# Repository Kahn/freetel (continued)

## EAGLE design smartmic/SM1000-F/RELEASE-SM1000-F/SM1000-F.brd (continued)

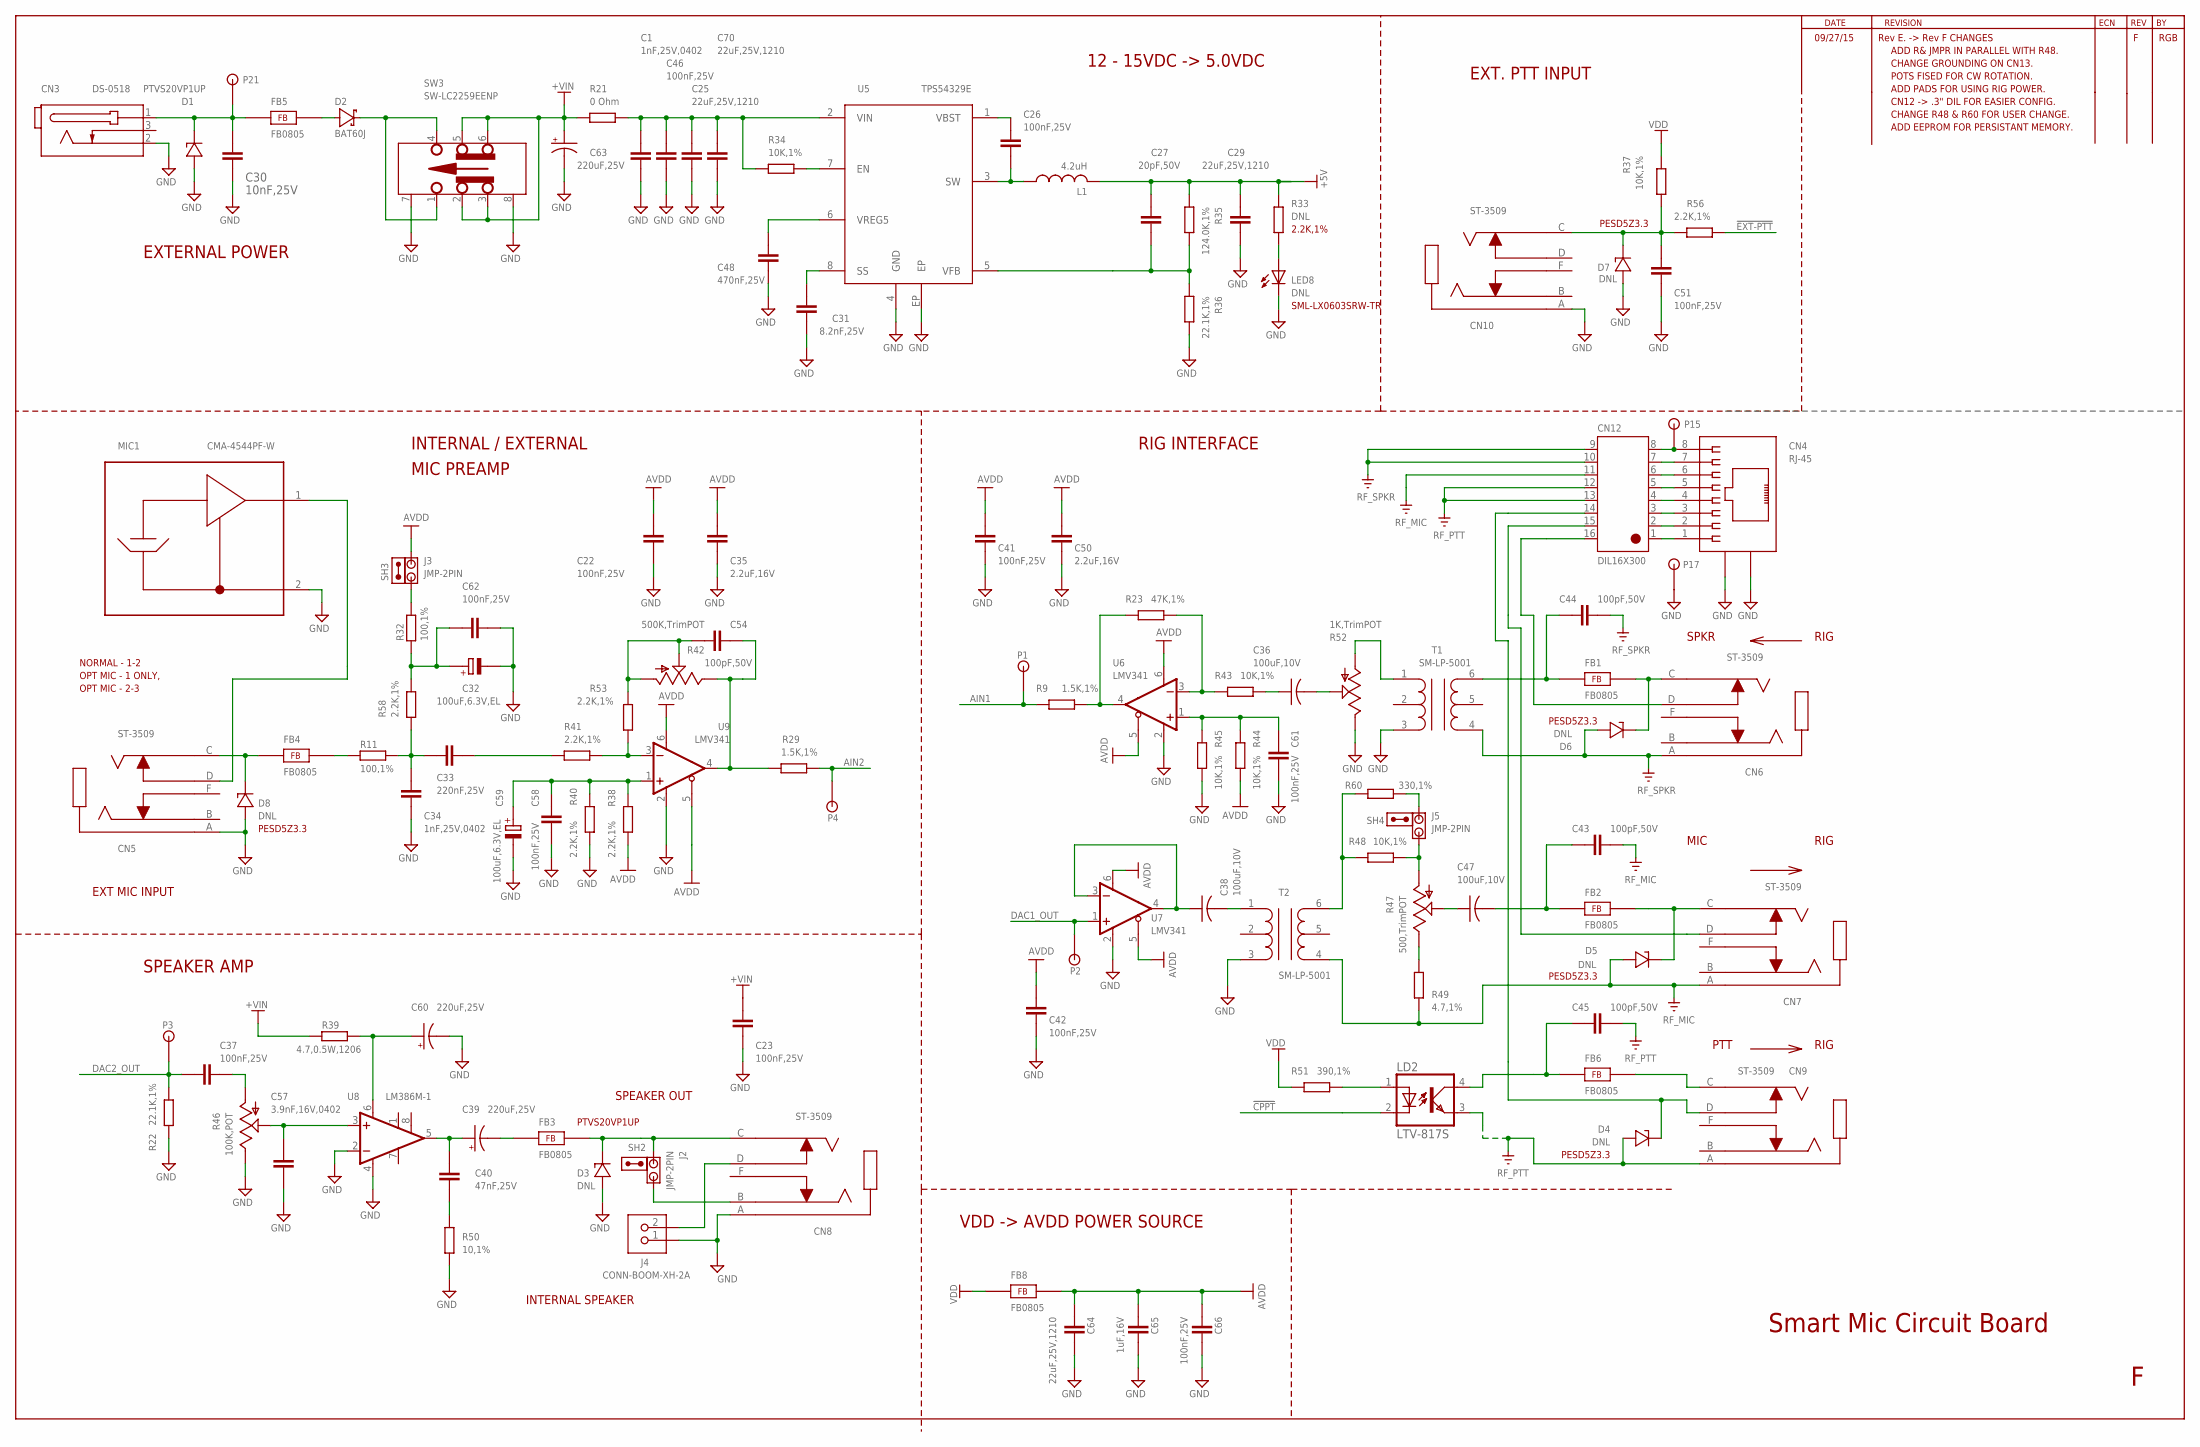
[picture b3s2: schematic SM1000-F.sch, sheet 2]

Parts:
C1, C34: 1nF,25V,0402; CAPC1005X60N
C22, C23, C26, C37, C41, C42, C46, C51, C58, C61, C62, C66: 100nF,25V; CAPC1005X60N
C25, C29, C64, C70: 22uF,25V,1210; CAPC3225X168N
C27: 20pF,50V; CAPC1005X60N
C30: 10nF,25V; CAPC1005X60N
C31: 8.2nF,25V; CAPC1608X92N
C32, C59: 100uF,6.3V,EL; NICHICON-WX-6.3
C33: 220nF,25V; CAPC1005X60N
C35, C50: 2.2uF,16V; CAPC1608X92N
C36, C38, C47: 100uF,10V; C1210
C39, C60, C63: 220uF,25V; CAP-CHEMI-HA0
C40: 47nF,25V; CAPC1005X60N
C43, C44, C45, C54: 100pF,50V; CAPC1005X60N
C48: 470nF,25V; CAPC1608X92N
C57: 3.9nF,16V,0402; CAPC1005X60N
C65: 1uF,16V; CAPC1608X92N
CN3: DS-0518
CN4: RJ-45; CONN-RJ45-MOLEX-44144-003
CN5, CN6, CN7, CN8, CN9, CN10: ST-3509
CN12: DIL16X300
D1: PTVS20VP1UP; SOD128
D2: BAT60J; SOD323R_INFINEON
D3: DNL; SOD128
D4, D5, D6, D7, D8: DNL; SOD523
FB1, FB2, FB3, FB4, FB5, FB6, FB8: FB0805; FE0805
J2, J3, J5: JMP-2PIN; JMPR-2PIN
J4: CONN-BOOM-XH-2A
L1: 4.2uH; SRR5028
LD2: LTV-817S
LED8: DNL; SML-LX0603SRW
MIC1: CMA-4544PF-W
P1, P2, P3, P4, P15, P17, P21: TPAD50
R9, R29: 1.5K,1%; RESC1005X40AN
R11, R32: 100,1%; RESC1608X55N
R21: 0 Ohm; RESC1608X55N
R22: 22.1K,1%; RESC1608X55N
R23: 47K,1%; RESC1005X40AN
R33: DNL; RESC1005X40AN
R34, R37, R43, R44, R45: 10K,1%; RESC1005X40AN
R35: 124.0K,1%; RESC1005X40AN
R36: 22.1K,1%; RESC1005X40AN
R38, R40, R41, R53, R56, R58: 2.2K,1%; RESC1005X40AN
R39: 4.7,0.5W,1206; RESC3115X70N
R42: 500K,TrimPOT; POT3361
R46: 100K,POT; POT-3310C
R47: 500,TrimPOT; POT3361
R48: 10K,1%; RESC3115X70N
R49: 4.7,1%; RESC1005X40AN
R50: 10,1%; RESC1608X55N
R51: 390,1%; RESC1005X40AN
R52: 1K,TrimPOT; POT3361
R60: 330,1%; RESC3115X70N
SH2, SH3, SH4: SHUNT,0.1IN; NOPACKAGE
SW3: SW-LC2259EENP; SW-LC2259
T1, T2: SM-LP-5001
U5: TPS54329E; PSO-DDA
U6, U7, U9: LMV341; SOT23-6
U8: LM386M-1; SO08

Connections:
!CPPT!: LD2.2 (C); also elsewhere on the board
!EXT-PTT!: R56.2; also elsewhere on the board
+5V: C27.1, C29.1, L1.2, R33.1, R35.1; also elsewhere on the board
+VIN: C23.1, C63.1, R21.1, R39.1, SW3.2, SW3.3, SW3.5, SW3.6; also elsewhere on the board
AIN1: P1.1, R9.1; also elsewhere on the board
AIN2: P4.1, R29.1; also elsewhere on the board
APTT: CN9.D, CN12.14, D4.C
AVDD: C22.1, C35.1, C41.1, C42.1, C50.1, C64.1, C65.1, C66.1, FB8.2, J3.2, R38.2, R44.2, U6.5 (!SHDN!), U6.6 (V+), U7.5 (!SHDN!), U7.6 (V+), U9.5 (!SHDN!), U9.6 (V+)
DAC1_OUT: P2.1, U7.1 (+IN); also elsewhere on the board
DAC2_OUT: C37.1, P3.1, R22.1; also elsewhere on the board
GND: C1.1, C22.2, C23.2, C25.2, C29.2, C30.2, C31.2, C32.2 (-), C34.2, C35.2, C41.2, C42.2, C46.2, C48.2, C50.2, C51.2, C57.2, C58.1, C59.2 (-), C60.2, C61.2, C62.2, C63.2, C64.2, C65.2, C66.2, C70.2, CN3.2, CN4.9, CN4.10, CN5.A, CN8.A, CN10.A, D1.A, D3.A, D7.A, D8.A, J4.1, LED8.C, MIC1.2, P17.1, R22.2, R36.2, R40.2, R45.2, R46.1, R50.2, R52.1, SW3.7, SW3.8, T1.3, T2.3, U5.4 (GND), U5.EP, U6.2 (GND), U7.2 (GND), U8.2 (-IN), U8.4 (GND), U9.2 (GND); also elsewhere on the board
MIC: CN7.D, CN12.15
unnamed: C39.1, C40.1, U8.5 (OUT)
unnamed: C36.2, R52.2
unnamed: C51.1, CN10.C, D7.C, R37.2, R56.1
unnamed: C26.1, U5.1 (VBST)
unnamed: D2.A, FB5.2
unnamed: C33.1, C34.1, R11.2, R58.1
unnamed: FB4.2, R11.1
unnamed: C54.2, R29.2, R42.1, U9.4 (OUT)
unnamed: J3.1, R32.2
unnamed: C27.2, R35.2, R36.1, U5.5 (VFB)
unnamed: R23.2, R43.1, U6.3 (-IN)
unnamed: C44.1, FB1.1, T1.6
unnamed: C37.2, R46.3
unnamed: C33.2, R41.1
unnamed: C1.2, C25.1, C46.1, C70.1, R21.2, R34.1, U5.2 (VIN)
unnamed: R9.2, R23.1, U6.4 (OUT)
unnamed: C31.1, U5.8 (SS)
unnamed: C57.1, R46.2, U8.3 (+IN)
unnamed: C48.1, U5.6 (VREG5)
unnamed: C54.1, R42.2, R42.3, R53.2
unnamed: R34.2, U5.7 (EN)
unnamed: C40.2, R50.1
unnamed: C39.2, FB3.1
unnamed: C32.1 (+), C62.1, R32.1, R58.2
unnamed: C58.2, C59.1 (+), R38.1, R40.1, U9.1 (+IN)
unnamed: LED8.A, R33.2
unnamed: C60.1, R39.2, U8.6 (VS)
unnamed: LD2.1 (A), R51.1
unnamed: C36.1, R43.2
unnamed: CN4.8, CN12.8, P15.1
unnamed: CN4.7, CN12.7
unnamed: CN4.6, CN12.6
unnamed: CN4.5, CN12.5
unnamed: CN4.4, CN12.4
unnamed: CN4.3, CN12.3
unnamed: CN4.2, CN12.2
unnamed: CN4.1, CN12.1
unnamed: C61.1, R44.1, R45.1, U6.1 (+IN)
unnamed: CN5.D, MIC1.1
unnamed: R47.1, R49.2
unnamed: CN8.C, D3.C, FB3.2, J2.2
unnamed: R52.3, T1.1
unnamed: CN8.B, J2.1
unnamed: C38.2, T2.1
unnamed: CN7.C, D5.C, FB2.2
unnamed: C38.1, U7.3 (-IN), U7.4 (OUT)
unnamed: CN8.D, J4.2
unnamed: CN9.C, FB6.2
unnamed: C45.1, FB6.1, LD2.4 (COL)
unnamed: J5.2, R60.1
unnamed: CN5.C, D8.C, FB4.1
unnamed: C30.1, CN3.1, D1.C, FB5.1, P21.1
unnamed: R48.2, R60.2, T2.6
unnamed: C43.1, C47.2, FB2.1
unnamed: C47.1, R47.2
unnamed: D2.C, SW3.1, SW3.4
unnamed: J5.1, R47.3, R48.1
unnamed: CN6.C, D6.C, FB1.2
unnamed: R41.2, R53.1, U9.3 (-IN)
RF_MIC: C43.2, CN7.A, CN12.11, D5.A, R49.1, T2.4
RF_PTT: C45.2, CN9.A, CN12.12, CN12.13, D4.A, LD2.3 (EMIT)
RF_SPKR: C44.2, CN6.A, CN12.9, CN12.10, D6.A, T1.4
SPKR: CN6.D, CN12.16
SW: C26.2, L1.1, U5.3 (SW)
VDD: FB8.1, R37.1, R51.2; also elsewhere on the board

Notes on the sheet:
SPKR
MIC
RIG
SPEAKER OUT
PTT
EXT MIC INPUT
EXTERNAL POWER
12 - 15VDC -> 5.0VDC
INTERNAL / EXTERNAL
MIC PREAMP
SPEAKER AMP
RIG INTERFACE
Smart Mic Circuit Board
NORMAL - 1-2
OPT MIC - 1 ONLY,
OPT MIC - 2-3
EXT. PTT INPUT
INTERNAL SPEAKER
VDD -> AVDD POWER SOURCE
2.2K,1%
SML-LX0603SRW-TR
PESD5Z3.3
PTVS20VP1UP
09/27/15
Rev E. -> Rev F CHANGES
ADD R& JMPR IN PARALLEL WITH R48.
CHANGE GROUNDING ON CN13.
POTS FISED FOR CW ROTATION.
ADD PADS FOR USING RIG POWER.
CN12 -> .3" DIL FOR EASIER CONFIG.
CHANGE R48 & R60 FOR USER CHANGE.
RGB
ADD EEPROM FOR PERSISTANT MEMORY.

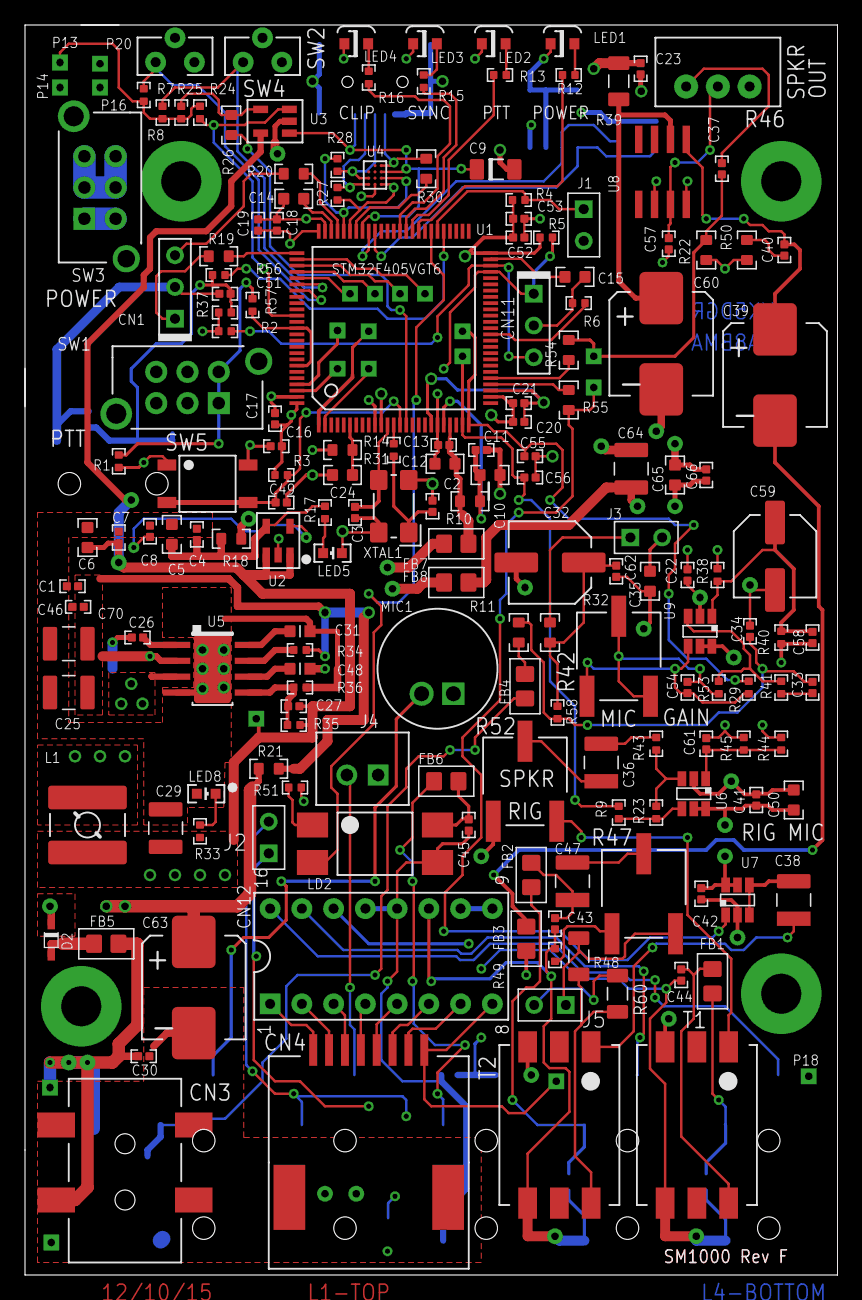
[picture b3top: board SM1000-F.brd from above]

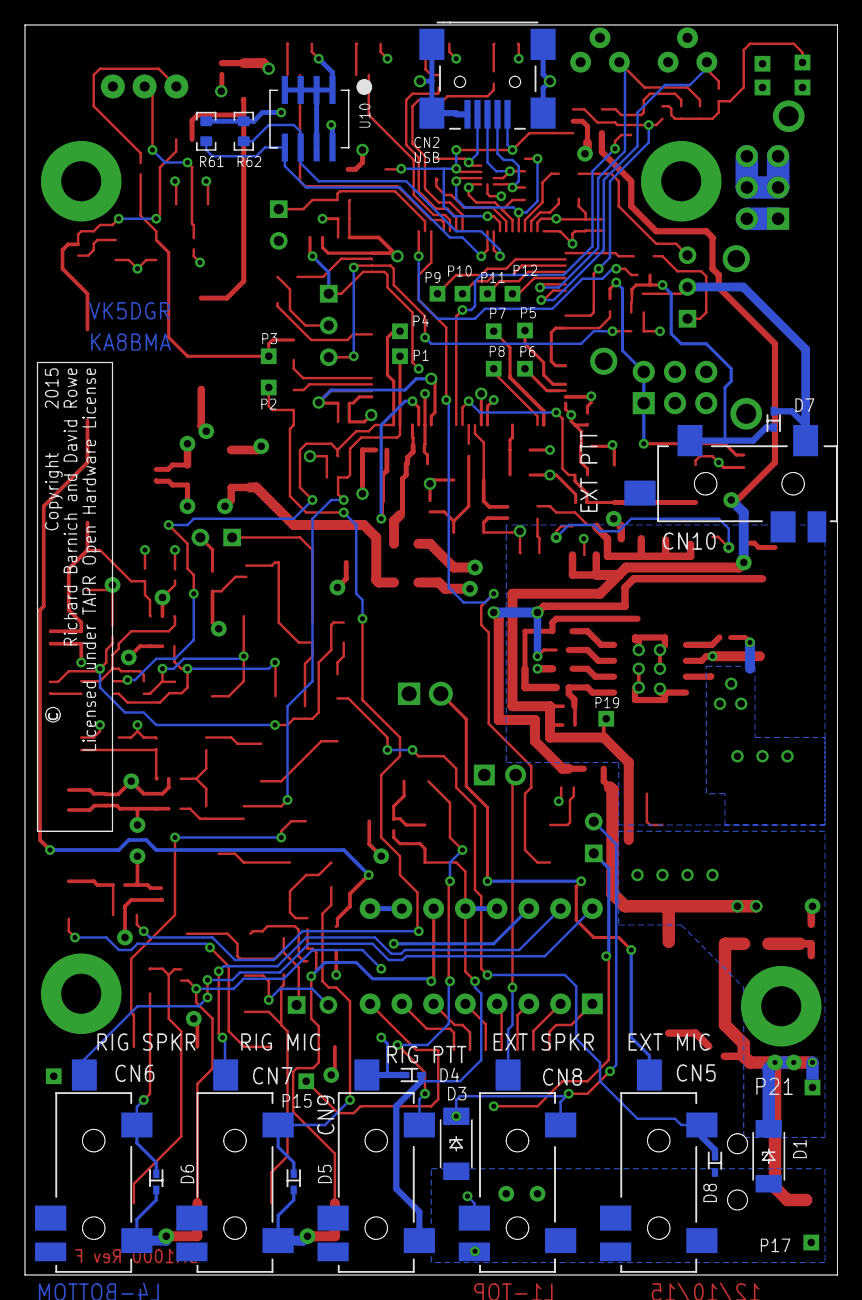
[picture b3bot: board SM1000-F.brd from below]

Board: 4 copper layers, 65.0 x 100.0 mm, 216 parts (33 on the bottom side), 131 nets.

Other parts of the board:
DRILEGEND: DRILEGEND
U$4: SWPS-OTL

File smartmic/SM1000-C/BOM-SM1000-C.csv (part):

"BILL OF MATERIAL FROM 310-0136A.SCH, 12 PARTS, GROUPED BY VALUES, AS OF 5/25/2010 2:37:49 PM"
"Part","Qty","DEFINITION","MANUFACTURER","MFG_NUMBER","DISTRIBUTOR","DIST_NUMBER","GENERIC","ROHS","COST100",
"C1, C34, C55, C56","4","CAP CER 1000PF 50V 10% X7R 0402","MURATA","GRM155R71H102KA01D","DIGIKEY","490-1303-1-ND","Y","Y","0.006"
"C2, C3, C27","3","CAP CER 20PF 50V 5% NP0 0402","SAMSUNG","CL05C200JB5NNNC","DIGIKEY","1276-1661-1-ND","Y","Y","0.005"
"C4, C7, C11, C13, C16, C18, C20, C22, C23, C26, C33, C37, C41, C42, C46, C49, C51, C52, C58, C61, C62, C66","22","CAP CER 0.1UF 25V Y5V 0402","MURATA","GRM155F51E104ZA01D","DIGIKEY","1276-1661-1-ND","Y","Y","0.003"
"C5, C6, C10, C12, C24, C65","6","CAP CER 1UF 16V 10% X5R 0603","YAEGO","CC0603KRX5R7BB105","DIGIKEY","311-1444-1-ND","Y","Y","0.033"
"C8, C17, C19, C21, C30, C53","6","CAP CER 10000PF 25V 20% X7R 0402","SAMSUNG","CL05B103MA5NNNC","DIGIKEY","1276-1503-1-ND","Y","Y","0.004"
"C9","1","CAP TANT 4.7UF 16V 10% 1206","AVX","TAJA475K016RNJ","DIGIKEY","478-3868-1-ND","Y","Y","0.260"
"C14, C15, C35, C50","4","CAP CER 2.2UF 16V 10% X5R 0603","TDK","C1608X5R1C225K080AB","DIGIKEY","445-5157-1-ND","Y","Y","0.0643"
"C25, C29, C64, C70","4","CAP CER 22UF 25V 10% X5R 1210","MURATA","GRM32ER61E226KE15L","DIGIKEY","490-3889-1-ND","N","Y","0.540"
"C31","1","CAP CER 8200PF 50V 10% X7R 0603","SAMSUNG","CL10B822KB8NNNC","DIGIKEY","1276-2119-1-ND","Y","Y","0.005"
"C32, C59","2","CAP ALUM 100UF 6.3V 20% SMD","NICHICON","UWX0J101MCL1GB","DIGIKEY","493-2088-1-ND","Y","Y","0.114"
"C36, C38, C47","3","CAP CER 100UF 10V 20% X5R 1210","SAMSUNG","CL32A107MPVNNNE","DIGIKEY","1276-3364-1-ND","Y","Y","0.735"
"C39, C60, C63","3","CAP ALUM 220UF 25V 20% SMD","UNITED CHEMI-CON","EMVY250ADA221MHA0G","DIGIKEY","565-2463-1-ND","N","Y","0.412"
"C40","1","CAP CER 0.047UF 25V 10% X7R 0402","TDK","445-4941-1-ND","DIGIKEY","445-4941-1-ND","Y","Y","0.015"
"C43, C44, C45, C54","4","CAP CER 100PF 50V 10% NP0 0402","SAMSUNG","CL05C101KB5NNNC","DIGIKEY","1276-1633-1-ND","Y","Y","0.005"
"C48","1","CAP CER 0.47UF 25V 10% X5R 0603","TDK","C1608X5R1E474K080AC","DIGIKEY","445-5144-1-ND","Y","Y","0.047"
"C57","1","CAP CER 3900PF 50V 10% X7R 0402","MURATA","GRM155R71H392KA01D","DIGIKEY","490-1307-1-ND","Y","Y","0.011"
"CN1, CN11","2","CONN HEADER 3POS .100 VERT GOLD","MOLEX","22-10-2031","DIGIKEY","WM2723-ND","N","Y",".495"
"CN2","1","MINIB USB CONN, SMT","JISEN","JS-MU3-002","JISEN","JS-MU3-002","N","Y","0.50"
"CN3","1","DC POWER CONN, FOR 2.1 X 5.5MM","YQLXDZ","DS-0518","YQLXDZ","DS-0518","N","Y","0.30"
"CN4","1","CONN MOD JACK R/A 8P8C","MOLEX","0441440003","DIGIKEY","WM4595CT-ND","N","Y","1.387"
"CN5, CN6, CN7, CN8, CN9, CN10","6","3.5mm STEREO, SWITCHED SMT CONN.","JISEN","ST-3509","JISEN","ST-3509","N","Y","0.20"
"CN12","1","CONN RECEPT 16POS 2MM GOLD DIP","HIROSE","A3C-16DA-2DSA(71)","DIGIKEY","H10897-ND","Y","Y","1.638"
"D1","1","DIODE SCHOTTKY 30V 0.5A 2TUMD","ROHM SEMI","RSX051VA-30TR","DIGIKEY","RSX051VA-30CT-ND","N","N","0.271"
"D2","1","DIODE SCHOTTKY 10V 3A SOD323","STM","BAT60JFILM","DIGIKEY","497-3707-1-ND","Y","Y","0.240"
"FB1, FB2, FB3, FB4, FB5, FB6, FB7, FB8","8","FERRITE 500MA 600 OHM 0805 SMD","lAIRD","HZ0805E601R-10","DIGIKEY","240-2399-1-ND","N","Y","0.0381"
"J1, J3, J4","3","CONN HEADER 2POS .100 VERT GOLD","MOLEX","22-28-4023","DIJIKEY","WM6502-ND","Y","Y","0.190"
"L1","1","INDUCTOR POWER 4.2UH 2.5A SMD","BOURNS","SRR5028-4R2Y","DIGIKEY","SRR5028-4R2YCT-ND","N","N","0.456"
"LD2","1","OPTOISOLATR 5KV TRANSISTOR 4-SMD","LITE-ON","LTV-817S-TA1","DIGIKEY","160-1893-1-ND","N","Y","0.217"
"LED1, LED2","2","LED SUPR RED CLR RT ANG 0805","LITE-ON","LTST-S220KRKT","DIGIKEY","160-1469-1-ND","Y","Y","0.1151"
"LED3","1","LED GREEN CLEAR RT ANG 0805","LITE-ON","LTST-S220KGKT","DIGIKEY","160-1468-1-ND","N","Y","0.135"
"LED4","1","LED YELLOW CLEAR RT ANG 0805","LITE-ON","LTST-S220KSKT","DIGIKEY","160-1470-1-ND","N","Y","0.143"
"LED5","1","LED 660NM SUPER RED DIFF 0603SMD","LITE-ON","SML-LX0603SRW-TR","DIGIKEY","67-1551-1-ND","Y","Y","0.169"
"LED8","1","LED SUPR RED CLR RT ANG 0805","LITE-ON","LTST-S220KRKT","DIGIKEY","160-1469-1-ND","Y","Y","0.1151"
"MIC1","1","MIC COND ANALOG OMNI -44DB","CUI","CMA-4544PF-W","DIGIKEY","102-1721-ND","N","Y","0.569"
"P1, P2, P3, P4, P5, P6, P7, P8, P9, P10, P11, P12, P13, P14, P16, P18, P19, P20","18","TEST PAD, .050","NA","NA","NA","NA","NA","NA","0.0"
"PCB1","1","PCB - SM1000 REV. C","TBD(PCB UNIVERSE)","TBD","TBD","TBD","N","Y","5.750"
"R1, R7, R8, R25, R34, R37, R43, R44, R45, R48","10","RES 10.0K OHM 1/16W 1% 0402 SMD","VISHAY-DALE","CRCW040210K0FKED","DIGIKEY","541-10.0KLCT-ND","Y","Y","0.017"
"R2, R3, R4, R5","4","RES 4.70K OHM 1/16W 1% 0402 SMD","VISHAY-DALE","CRCW04024K70FKED","DIGIKEY","541-4.70KLCT-ND","Y","Y","0.026"
"R6, R17","2","RES 1.00K OHM 1/16W 1% 0402 SMD","VISHAY-DALE","CRCW04021K00FKED","DIGIKEY","541-1.00KLCT-ND","Y","Y","0.026"
"R9, R29","2","RES 1.50K OHM 1/16W 1% 0402 SMD","VISHAY-DALE","CRCW04021K50FKED","DIGIKEY","541-1.50KLCT-ND","Y","Y","0.026"
"R10","1","RES 47.0 OHM 1/10W 1% 0603 SMD","VISHAY-DALE","CRCW060347R0FKEA","DIGIKEY","541-47.0HCT-ND","Y","Y","0.025"
"R11, R32","2","RES 100 OHM 1/10W 1% 0603 SMD","VISHAY","CRCW0603100RFKEA","DIGIKEY","541-100HCT-ND","Y","Y","0.030"
"R12, R13, R15, R16","4","RES 680 OHM 1/16W 1% 0402 SMD","VISHAY-DALE","CRCW0402680RFKED","DIGIKEY","541-680LCT-ND","Y","Y","0.026"
"R14","1","RES 220 OHM 1/16W 1% 0402 SMD","VISHAY-DALE","CRCW0402220RFKED","DIGIKEY","541-220LCT-ND","Y","Y","0.026"
"R18, R21, R26, R30, R31, R54, R55","7","RES 0.0 OHM 1/10W JUMP 0603 SMD","VISHAY-DALE","CRCW06030000Z0EA","DIGIKEY","541-0.0GCT-ND","Y","Y","0.025"
"R19, R20","2","RES 22.0 OHM 1/10W 1% 0603 SMD","VISHAY-DALE","CRCW060322R0FKEA","DIGIKEY","541-22.0HCT-ND","Y","Y","0.025"
"R22","1","RES 22.1K OHM 1/10W 1% 0603 SMD","VISHAY-DALE","CRCW060322K1FKEA","DIGIKEY","541-22.1KHCT-ND","Y","Y","0.025"
"R23, R24","2","RES 47.0K OHM 1/16W 1% 0402 SMD","VISHAY-DALE","CRCW040247K0FKED","DIGIKEY","541-47.0KLCT-ND","Y","Y","0.026"
"R27, R28","2","RES 22.0 OHM 1/16W 1% 0402 SMD","VISHAY-DALE","CRCW040222R0FKED","DIGIKEY","541-22.0LCT-ND","Y","Y","0.026"
"R33, R38, R40, R41, R53, R56, R58","7","RES 2.20K OHM 1/16W 1% 0402 SMD","VISHAY-DALE","CRCW04022K20FKED","DIGIKEY","541-2.20KLCT-ND","Y","Y","0.017"
"R35","1","RES 124K OHM 1/16W 1% 0402 SMD","VISHAY-DALE","CRCW0402124KFKED","DIGIKEY","541-124KLCT-ND","Y","Y","0.044"
"R36","1","RES 124K OHM 1/16W 1% 0402 SMD","VISHAY-DALE","541-22.1KLCT-ND","DIGIKEY","541-22.1KLCT-ND","Y","Y","0.026"
"R39","1","RES 4.70 OHM .5W 1% 1206 SMD","VISHAY DALE","CRCW12064R70FKEAHP","DIGIKEY","541-4.70UCT-ND","Y","Y","0.225"
"R42","1","TRIMMER 500K OHM 0.2W SMD","PANASONIC","EVM-1DSX30B55","DIGIKEY","P1D504CT-ND","Y","Y","0.339"
"R46","1","POT 100K OHM 9MM SQ RTANG PLAST","BOURNS","3310C-001-104L","DIGIKEY","3310C-001-104L-ND","N","Y","1.920"
"R47","1","TRIMMER 500 OHM 0.2W SMD","PANASONIC","EVM-1DSX30B52","DIGIKEY","P1D501CT-ND","Y","Y","0.339"
"R49","1","RES 4.7 OHM 1/16W 5% 0402 SMD","VISHAY-DALE","541-4.7JCT-ND","DIGIKEY","541-4.7JCT-ND","Y","Y","0.023"
"R50","1","RES 10.0 OHM 1/10W 1% 0603 SMD","VISHAY-DALE","CRCW060310R0FKEA","DIGIKEY","541-10.0HCT-ND","Y","Y","0.025"
"R51","1","RES 390 OHM 1/16W 1% 0402 SMD","VISHAY-DALE","CRCW0402390RFKED","DIGIKEY","541-390LCT-ND","Y","Y","0.044"
"R52","1","TRIMMER 1K OHM 0.2W SMD","PANASONIC","EVM-1DSX30B13","DIGIKEY","P1D102CT-ND","Y","Y","0.339"
"R57","1","RES 470 OHM 1/16W 1% 0402 SMD","VISHAY-DALE","CRCW0402470RFKED","DIGIKEY","541-470LCT-ND","Y","Y","0.044"
"SH1, SH3","2","SHUNT LP 2 POS SN","TYCO AMP","1-382811-6","DIGIKEY","A26231-ND","Y","Y","0.210"
"SPKR1","1","SPKR, 40mm,8Ohm","SHENZHEN HY ELECTRON","HY4004M-001","SHENZHEN HY ELECTRON","HY4004M-001","N","Y","0.50"
"SW1, SW2, SW4","3","4.5X4.5mm TACTILE SWIRCH RA TH","YQLXDZ","TS-026","YQLXDZ","TS-026","N","Y","0.05"
"SW3","1","SWITCH PUSH DPDT 0.1A 30V","E-SWITCH","PBH2UEENAGX","DIGIKEY","EG2655-ND","N","Y","1.332"
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
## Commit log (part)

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2017-01-12 debugging codec2.c mode
2017-01-12 debugging phase on decode using c2sim
2017-01-12 700C lives :-)
2017-01-12 removed debug stuff
2017-01-13 Fixed freedv_tx issue on 2400A
2017-01-13 Fixed 800XA and switched over to the new 700C mode
2017-01-13 700B working again, still need to fix test frame mode
2017-01-13 FreeDV 700C mode working
2017-01-13 support for 700c and 800xa
2017-01-14 correct sample rate fpor 700 B&C
2017-01-14 refactored FSK modes so it works with complex inputs
2017-01-14 800XA decoding OK
2017-01-14 Fixed stat copying for 800XA
2017-01-15 refactored stats handling for fsk and fmfsk to be consistent with other modems, freedv_api, and FreeDV GUI. Tested freedv_tx/rx with 2400A/2400B/800XA. Still need to test GUI output, e.g. for fsk_dem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
2017-01-15 Jeroen's energy patch for 700C - thanks
2017-01-15 Jeroen's suggestion to minimise processing delay for 700C, also updated Octave and C unittests for C port - thanks Jeroen
2017-01-15 added option for normalisation of fsk eye diagram samples
2017-01-15 first pass at eye diagram for 800XA
2017-01-16 modified fsk get/put test frame utils so that they can re-sync on a continuous stream, updated README examples
2017-01-17 output stats after each frame, useful for streaming operation
2017-01-18 working up 700c link budget
2017-01-18 added mode for demodulating 800XA waveform
2017-01-18 first pass at OQPSK simulation
2017-01-18 calibrated EB/No and BER, about to add sync algs
2017-01-18 timing and phase sync working OK with noise
2017-01-18 started phase ambiguity and impairment testing
2017-01-18 fixed bug in timing angle to offset estimation, in the middle of refactoring BER est for phase ambiguity
2017-01-19 current state, but having some problems with timing and phase offset interactions
2017-01-19 prototype UW sync on sep I and Q
2017-01-19 logic for working out I and Q swap and sign changes on I & Q due to phase rotations
2017-01-19 a little clen up for blog post
2017-01-20 moved 800XA start tome to 880Hz and adjusted tx rms power to match 1600 and 700 waveforms
2017-01-20 updated README on how to find DLLs
2017-01-20 plug in menu options noe depend on presence of plugin
2017-01-20 disable some more plug in code when plugin not present
2017-01-25 made tsrc a little more generic
2017-01-26 added linear and complex resampling options
2017-01-26 Tweaks for MinGW. Still a work in progress.
2017-01-27 fixed array overrun bug spotted by Steve - thanks Steve
2017-01-28 minimal set of sox 14.4.1 source files we need; unit test builds and runs OK
2017-01-28 first pass at including sox source files, still haven't removed external libsox lib
2017-01-28 builds and runs OK on Linux with internal sox library files, speaker eq tested, README updated for no sox, modfied positioningof audio setup dialog so OK not hidden off screen
2017-01-28 simple linear interpolator
2017-01-28 added complex samples
2017-01-29 Fix building of internal sox on MinGW. Add logic to pickup depdendency on libwinpthread on MinGW.
2017-01-30 added 8 bit signed ouput example, scatter looks OK
2017-01-30 added interp/dec resamplers
2017-01-30 optional Fs/4 freq shift and some optimisation of tlininterp
2017-01-30 fixed bug in block based output, scatter looks OK, and about 10% CPU load for tx
2017-01-31 fix for helicopter noise on 700 plus Mooner's patch for OSX
2017-01-31 converted eb/no to snt est and added squelch to 800xa
2017-02-02 changed click to tune to double click to prevent accidental freq shifts
2017-02-03 CMA FSK equaliser simulation
2017-02-03 updated BER reporting
2017-02-03 correct incldue file
2017-02-03 fixed calculation of RF bandwidth thanks Steve
2017-02-06 instructions for building without sox
2017-02-06 modified 1600 so it doesn't alter amplitude of the demod input vector, to allow pass thru when not squelched, makes local copy now
2017-02-06 Remove conditional around build type for whether dev tools should be built or not. Removes dependency on speex for non-dev builds.
2017-02-07 another go at squench for 800XA
2017-02-07 removed unsed code that was generating warnings
2017-02-07 removed some warnings gcc 6 picked up
2017-02-07 make update rate of spectrum and waterfall indep of mode, thanks Tony for help in discovering this one
2017-02-08 Add logic for older gcc in RHEL 6 which doesn't understand -std=gnu11.
2017-02-09 used to generate figures for HF modem design blog post
2017-02-10 initial checkin, QPSK theory and experimental
2017-02-13 all curves up to HF working, about to change from 1 sample per symbol to M samples/symbol for diversity
2017-02-14 hackrf testing util
2017-02-14 hackrf test util
2017-02-14 clean up help
2017-02-14 Updated method of detecting dependencies for MinGW builds.
2017-02-15 Branch and tag codec2 0.6
2017-02-15 Commit branch and tag of FreeDV 1.2
2017-02-17 started adding support for measuring BER from pilots, just added phase correction for pilots and nothing broke
2017-02-17 measuring BER from pilots in Octave OK
2017-02-18 discovered BER measurement using pilots can't work as pilots get rotated away from axis, so rolling back to previous working versions
2017-02-21 A bit more work on the TDMA header
2017-02-21 starting to instrument to further develop 700C. Added SNR field to channel settings, bar graphs for bit error counting on test frames, option to view 700C scatter before diversity combination, immedi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
2017-02-21 A bit more work on the TDMA header and notes
2017-02-21 added log graticule and scale, histograms testing out well
2017-02-21 cleaned up README a bit, added alsa loopback instructions
2017-02-22 Updated frame design slightly for TDMA
2017-02-22 improved formatting of bit mapping table
2017-02-23 added support for measuring bit errors before diversity combination, part of 700C instrumentation
2017-02-23 GUI support for bit error plot/historam before diversity combination, working OK on test using alsa loopback, part of 700C instrumentation
2017-02-23 1600 test frame hitsogram working again
2017-02-24 cohpsk and freedv API support for attenuating once carrier for 700C test purposes
2017-02-24 added FreeDV GUI support for attenuating one carrier, tested OK, and mapping of carriers to bit error plots and histograms checkes out
2017-02-24 Update C standard flag logic as gnu99 is the minimum required.
2017-02-24 tweaks to fix C99 issues
2017-03-02 re-enabled unittest building in Cmake & fixed C99 build issue
2017-03-05 first pass at option to introduce interfering carrier
2017-03-07 Updates to support OSX.
2017-03-13 Add libsamplerate as a cmake dependency for codec2.
2017-03-15 simulation to plot error curves for BIll VK5DSP's short LDPC codes
2017-03-15 short LPDC codes
2017-03-16 removed some unused old codebook files
2017-03-16 fix some warnings
2017-03-16 fix some warnings, remove unused ancient unittests
2017-03-16 first pass a AWGN perf curves for Bill's short codes
2017-03-16 modified plots for blog post
2017-03-16 added hf/multipath model, and diversity results
2017-03-18 better plot output, but not satisfied by fuzzy ouput of eps->png conversion
2017-03-18 break LDPC code->headerfile func out of ldpc_fsk_lib.m
2017-03-18 typo in header
2017-03-18 traps wrong CML path
2017-03-19 112 LDPC code support in LDPC unit tests
2017-03-19 ldpc_dec modified to read in half frames and perform FEC frame sync, cohpsk and unit tests modified to work with non-diversity, next step verify cohpsk with AWGN and test on cmd line with LDPC decoder
2017-03-19 README cleanup, still needs some work.
2017-03-19 Clean up how SVN revision works.
2017-03-19 soft dec output, ready for LDPC dec
2017-03-19 better support for multiple LDPC codes
2017-03-20 updated command line examples
2017-03-21 bpsk simulation with ML dbpsk and mod stripping phase est
2017-03-21 building up simulation to inlude phase and frequency offsets
2017-03-21 added worksheet for new BPSK waveform, nice results on paper
2017-03-23 working on handling phase est ambiguity neat +/- pi/2
2017-03-23 baseline rate Rs BPSK AWGN simulation, about to add HF
2017-03-24 can now simulate avergaing three carriers, about to speed up for longer tests
2017-03-29 first pass at pilot based phase estimation averaged over three carriers
2017-03-30 if-deffed out code not rqd for stm32 build
2017-04-04 added modn stripping refinemeant and wider time window options
2017-04-04 refactored to gives constant run time for different pilot insertion rates
2017-04-04 generates figures of various options
2017-04-04 Disable building GUI tools for wxWidgets since we don't need them.
2017-04-04 edited to support new cohpsk_mod API
2017-04-04 update pkgconfig template for codec2.
2017-04-07 progressing rate Fs bpsk ofdm simulation
2017-04-10 added BIll's ml_pd and comparedwith some curves
2017-04-10 converted to QPSK
2017-04-11 drawing curves
2017-04-15 timing and freq aquisition test
2017-04-19 progressing fine timing algorithm, added test based on small deviations from current timing est
2017-04-19 fine timing doing some sensible things, tracking timing as multipath changes, however BER still a little worse than fixed fine timing
2017-04-20 fine timing getting gd results (almost no IL) with no sample clock errors, and acceptable results at +/-500 and +/-1000ppm
2017-04-23 starting to refactor rate Fs ofdm simulation, and changed name of rate fs and rate rs
2017-04-26 refactoring rx side - rx sym not working on fixed buf,HF results looking gd
2017-04-26 fine timing and fine freq working on fixed buf
2017-04-27 cleaned up, next step put demod in function
2017-04-27 moved demodulation to phase correction loop
2017-04-27 cleaned up loop indexes
2017-04-28 code for handling sample slips, tested with +/-500ppm clock offsets
2017-04-29 moved buffer shift inside ofdm_demod, default init of run time states
2017-04-29 linker mods to reduce file of sm1000 binary - thanks Steve
2017-04-29 split rate fs ofdm simulation into multiple files
2017-04-29 first pass at file based rx
2017-04-29 first pass at file based tx
2017-04-30 error that was casuing sm1000 to crash - need one extra storage for phase H[]
2017-05-01 ofdm_tx and ofdm_rx working with no noise
2017-05-02 first pass coarse timing/frame sync working on ofdm_rx
2017-05-03 added AWGN and HF channel simulation, usual confusion with real signals, SNR est and meas. How rx is syncing up OK
2017-05-03 aquisition working with freq offsets up to +/-20Hz. A bit slow, but gd enough for initial OTA tests. Will speed up later.
2017-05-03 URL change, thanks Steve
2017-05-04 changed amplitde scaling to prevent clipping with noise
2017-05-04 first pass at LDPC integration. Good results for AWGN channel, but HF fading not working properly
2017-05-05 added fading channel model, results check out ok
2017-05-07 diabled writing log file on Win32
2017-05-07 modified to test Bill's short LDPC codes
2017-05-07 added ldpc code
2017-05-07 added better HF model which reconciled (poor) perf with ldpcut
2017-05-07 added a few notes and tested
2017-05-09 brought ldpcut back to a simplified demo for blog post
2017-05-10 interleaver working better, at least for ldpc_short, getting PER<0.1 at 6dB for 576*4 codewords on ldpc_qpsk and for 32 fr interleaver on ldpc_short
2017-05-11 script to separate all.wav into separate wave files for listening tests
2017-05-12 adding multiple LDPC frame interleaving, reorganised plots
2017-05-13 added various new plots for characterising system, added diversity for comparison, normalised HF power, slower freq tracking to improve perf
2017-05-13 one frame ldpc enc/dec working for ofdm_rx/ofdm_tx
2017-05-16 added rate 0.8 wenet ldpc code for comparison
2017-05-16 added error pattern and analog simulation
2017-05-16 added analog signal simulation and interleaving of (224,112) code, and a basic sync system for rx
2017-05-16 selects Nc based on code rate to maintain 700 bit/s payload data rate
2017-05-18 ssb filtering feature and bcleaned up rx logs
2017-05-18 thicker lines on plots
2017-05-25 Add bintray deployment
2017-05-25 Updates for bintray deploy
2017-05-25 bump travis
